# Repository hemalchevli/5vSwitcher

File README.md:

5vSwitcher
==========

Drop in replacement for 7805, step down voltage switcher.
This work is licensed under CC BY SA 4.0
http://creativecommons.org/licenses/by-sa/4.0/

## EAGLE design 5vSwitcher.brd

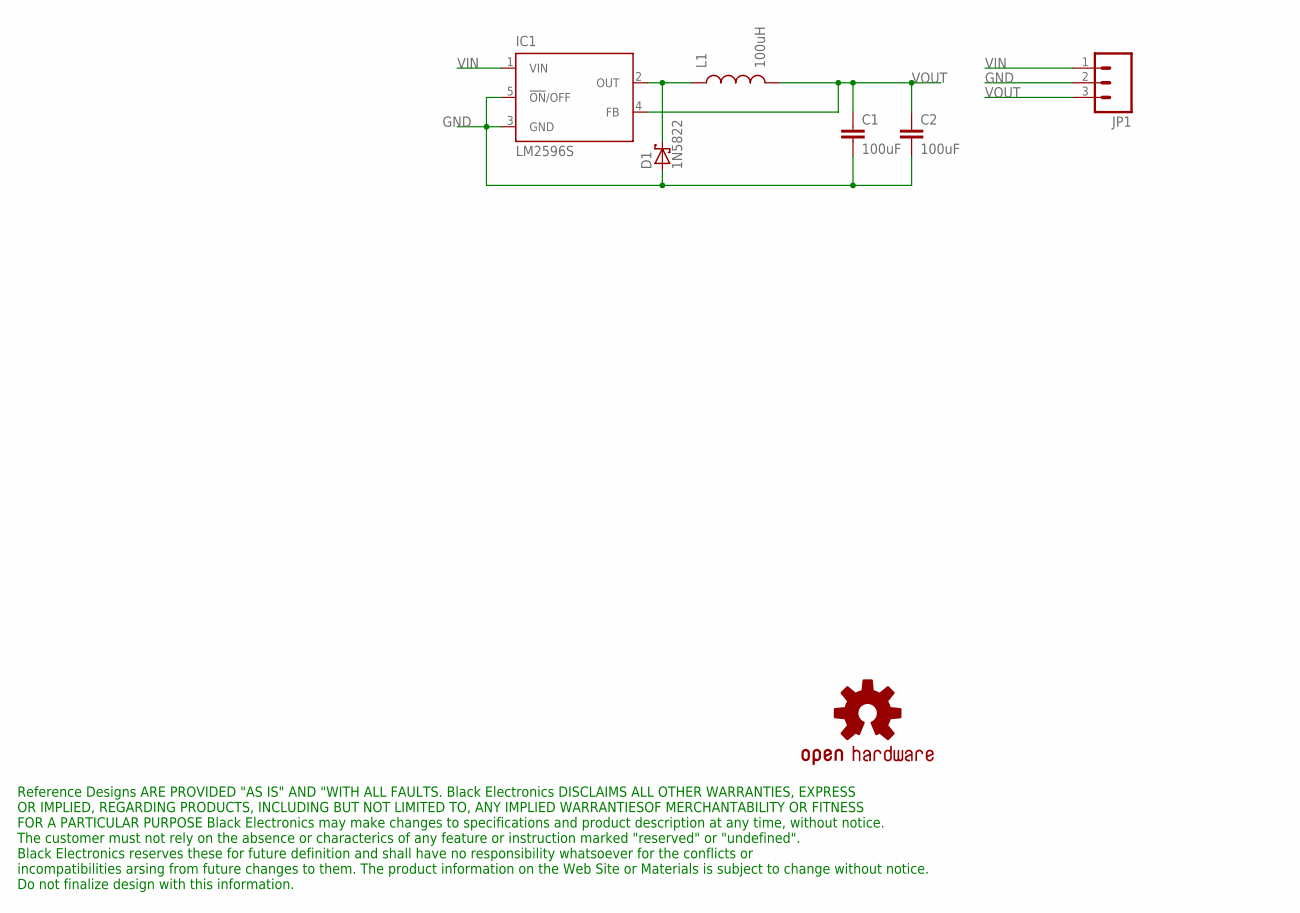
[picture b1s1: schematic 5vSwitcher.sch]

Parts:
C1, C2: 100uF; 0805
D1: 1N5822; SMC
IC1: LM2596S; TO263-5
JP1: M03PTH; 1X03
L1: 100uH; INDUCTOR-1206
U$1: OSHW-LOGOS; OSHW-LOGO-S

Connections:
GND: C1.2, C2.2, D1.A, IC1.3 (GND), IC1.5 (!ON!/OFF), JP1.2
unnamed: D1.C, IC1.2 (OUT), L1.P$1 (1)
VIN: IC1.1 (VIN), JP1.1
VOUT: C1.1, C2.1, IC1.4 (FB), JP1.3, L1.P$2 (2)

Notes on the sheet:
Reference Designs ARE PROVIDED "AS IS" AND "WITH ALL FAULTS. Black Electronics DISCLAIMS ALL OTHER WARRANTIES, EXPRESS OR IMPLIED, REGARDING PRODUCTS, INCLUDING BUT NOT LIMITED TO, ANY IMPLIED WARRANTIESOF MERCHANTABILITY OR FITNESS FOR A PARTICULAR PURPOSE Black Electronics may make changes to spe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

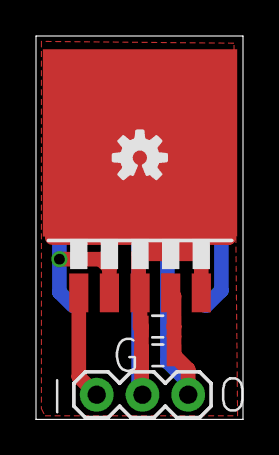
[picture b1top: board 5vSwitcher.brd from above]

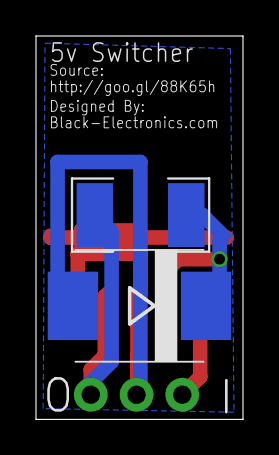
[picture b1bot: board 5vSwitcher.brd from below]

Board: 2 copper layers, 11.5 x 21.3 mm, 7 parts (2 on the bottom side), 4 nets.

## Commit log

2014-06-26 Update README.md with licence
2014-06-26 Added sch
2014-06-26 Added notice
2014-07-04 Clean up
2014-07-04 Added board file

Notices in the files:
parts and their libraries:
SparkFun: Licensing: CC v3.0 Share-Alike You are welcome to use this library for commercial purposes.
